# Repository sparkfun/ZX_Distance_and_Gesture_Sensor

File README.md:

**NOTE:** *This product has been retired from our catalog. If you are looking for more up-to-date info, please check out some of these resources to see how other users are still hacking and improving on this product.*
* *[SparkFun Forum](https://forum.sparkfun.com/)*
* *[Comments Here on GitHub](https://github.com/sparkfun/ZX_Distance_and_Gesture_Sensor/issues)*
* *[IRC Channel](https://www.sparkfun.com/news/263)*

There is another version available with the surface mount ICs [ ZX Distance and Gesture Sensor SMD - [SEN-13162](https://www.sparkfun.com/products/13162) ] so the associated Arduino Library will be kept open => [SparkFun_ZX_distance_and_Gesture_Sensor_Arduino_Library](https://github.com/sparkfun/SparkFun_ZX_Distance_and_Gesture_Sensor_Arduino_Library). 

SparkFun ZX Distance and Gesture Sensor
========================================

[*SparkFun ZX Distance and Gesture Sensor (SEN-12780)*](https://www.sparkfun.com/products/12780)

Infrared sensor capable of determining an object's distance from the sensor and its relative position between the IR LEDs. The sensor is capable of determining a 2-dimensional location of an object as well as determining several basic gestures.

Repository Contents
-------------------

* **/Hardware** - Eagle design files (.brd, .sch)
* **/Libraries** - Libraries for use with the ZX Distance and Gesture Sensor
* **/Production** - Production panel files (.brd)

Documentation
--------------

* **[Library](https://github.com/sparkfun/SparkFun_ZX_Distance_and_Gesture_Sensor_Arduino_Library)** - Arduino library for the ZX Distance and Gesture Sensor.
* **[Hookup Guide](https://learn.sparkfun.com/tutorials/zx-distance-and-gesture-sensor-hookup-guide)** - Basic hookup guide for the ZX Distance and Gesture Sensor.
* **[SparkFun Fritzing repo](https://github.com/sparkfun/Fritzing_Parts)** - Fritzing diagrams for SparkFun products.

Product Versions
----------------

* [SEN-12780](https://www.sparkfun.com/products/12780)- ZX Distance and Gesture Sensor

Version History
---------------

* [H_1.0_L_1.0.2](https://github.com/sparkfun/ZX_Distance_and_Gesture_Sensor/tree/H_1.0_L_1.0.2) - Fixed Arduino library name
* [H_1.0_L_1.0.1](https://github.com/sparkfun/ZX_Distance_and_Gesture_Sensor/tree/H_1.0_L_1.0.1) - Fixed typo in Arduino library properties file
* [H_1.0_L_1.0.0](https://github.com/sparkfun/ZX_Distance_and_Gesture_Sensor/tree/H_1.0_L_1.0.0) - Initial release

License Information
-------------------

This product is _**open source**_! 

Please review the LICENSE.md file for license information. 

If you have any questions or concerns on licensing, please contact techsupport@sparkfun.com.

Distributed as-is; no warranty is given.

- Your friends at SparkFun.

_This is a collaboration with [XYZ Interactive](http://www.gesturesense.com/xyz)_

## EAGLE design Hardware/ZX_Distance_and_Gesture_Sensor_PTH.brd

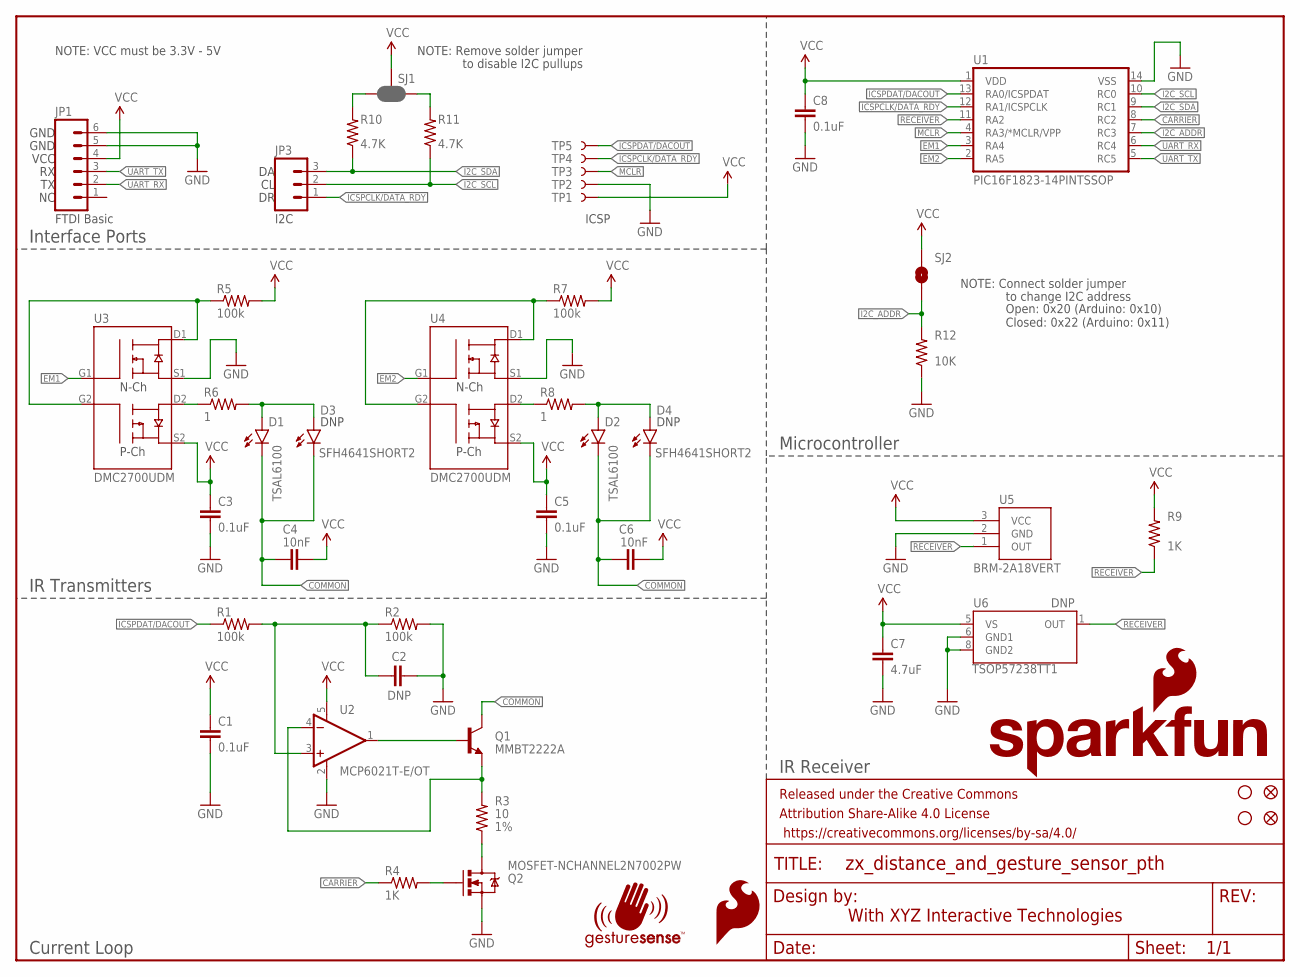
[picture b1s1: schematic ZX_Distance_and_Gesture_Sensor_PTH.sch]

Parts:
C1, C3, C5, C8: 0.1uF; 0603-CAP
C2: DNP; 0603-CAP
C4, C6: 10nF; 0603-CAP
C7: 4.7uF; 0603-CAP
D1, D2: LED-IR-THRUTSAL6100; LED5MM
D3, D4: SFH4641SHORT2; SFH4641-SHORT2
FID1, FID2: FIDUCIAL1X2; FIDUCIAL-1X2
FRAME1: FRAME-LETTER; CREATIVE_COMMONS
JP1: M06NO_SILK_FEMALE_PTH; 1X06_NO_SILK
JP3: M031X03_NO_SILK; 1X03_NO_SILK
LOGO1: SFE_LOGO_FLAME.1_INCH; SFE_LOGO_FLAME_.1
Q1: MMBT2222A; SOT23-3
Q2: MOSFET-NCHANNEL2N7002PW; SOT323
R1, R2, R5, R7: 100k; 0603-RES
R3: 10; 0603-RES
R4, R9: 1K; 0603-RES
R6, R8: 1; 0603-RES
R10, R11: 4.7K; 0603-RES
R12: 10K; 0603-RES
SJ1: JUMPER-PAD-3-NC_BY_PASTE; PAD-JUMPER-3-NC_BY_PASTE_YES_SILK_FULL_BOX
SJ2: JUMPER-PAD-2-NOYES_SILK; PAD-JUMPER-2-NO_YES_SILK
STANDOFF1, STANDOFF2: STAND-OFF
TP1, TP2, TP3, TP4, TP5: TEST-POINT3X4; PAD.03X.04
U1: PIC16F1823-14PINTSSOP; TSSOP14
U2: MCP6021T-E/OT; SOT23-5
U3, U4: DMC2700UDM; SOT26
U5: BRM-2A18VERT; BRM-2508_VERT
U6: TSOP57238TT1; TSOP572
U$5: SFE_LOGO_NAME_FLAME.1_INCH; SFE_LOGO_NAME_FLAME_.1
U$6: GESTURESENSE_LOGOSTEXT; GESTURESENSE_TEXT

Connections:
CARRIER: R4.1, U1.8 (RC2)
COMMON: C4.1, C6.1, D1.K (C), D2.K (C), D3.C, D4.C, Q1.3 (C)
EM1: U1.3 (RA4), U3.G1
EM2: U1.2 (RA5), U4.G1
GND: C1.2, C2.2, C3.2, C5.2, C7.2, C8.2, JP1.5, JP1.6, Q2.2 (S), R2.2, R12.1, TP2.P$1, U1.14 (VSS), U2.2 (V-), U3.S1, U4.S1, U5.2 (GND), U6.6 (GND1), U6.8 (GND2)
I2C_ADDR: R12.2, SJ2.1, U1.7 (RC3)
I2C_SCL: JP3.2, R11.1, U1.10 (RC0)
I2C_SDA: JP3.3, R10.1, U1.9 (RC1)
ICSPCLK/DATA_RDY: JP3.1, TP4.P$1, U1.12 (RA1/ICSPCLK)
ICSPDAT/DACOUT: R1.1, TP5.P$1, U1.13 (RA0/ICSPDAT)
MCLR: TP3.P$1, U1.4 (RA3/*MCLR/VPP)
unnamed: C2.1, R1.2, R2.1, U2.3 (+IN)
unnamed: Q1.2 (E), R3.2, U2.4 (-IN)
unnamed: Q1.1 (B), U2.1 (OUT)
unnamed: Q2.3 (D), R3.1
unnamed: Q2.1 (G), R4.2
unnamed: R6.1, U3.D2
unnamed: D1.A, D3.A, R6.2
unnamed: R5.1, U3.D1, U3.G2
unnamed: R7.1, U4.D1, U4.G2
unnamed: R10.2, SJ1.3
unnamed: R8.1, U4.D2
unnamed: D2.A, D4.A, R8.2
unnamed: R11.2, SJ1.1
RECEIVER: R9.1, U1.11 (RA2), U5.1 (OUT), U6.1 (OUT)
UART_RX: JP1.2, U1.6 (RC4)
UART_TX: JP1.3, U1.5 (RC5)
VCC: C1.1, C3.1, C4.2, C5.1, C6.2, C7.1, C8.1, JP1.4, R5.2, R7.2, R9.2, SJ1.2, SJ2.2, TP1.P$1, U1.1 (VDD), U2.5 (V+), U3.S2, U4.S2, U5.3 (VCC), U6.5 (VS)

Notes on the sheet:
With XYZ Interactive Technologies
FTDI Basic
I2C
ICSP
NOTE: Remove solder jumper
to disable I2C pullups
NOTE: Connect solder jumper
to change I2C address
Open: 0x20 (Arduino: 0x10) Closed: 0x22 (Arduino: 0x11)
Interface Ports
IR Transmitters
Current Loop
Microcontroller
IR Receiver
VCC
GND
DNP
NOTE: VCC must be 3.3V - 5V

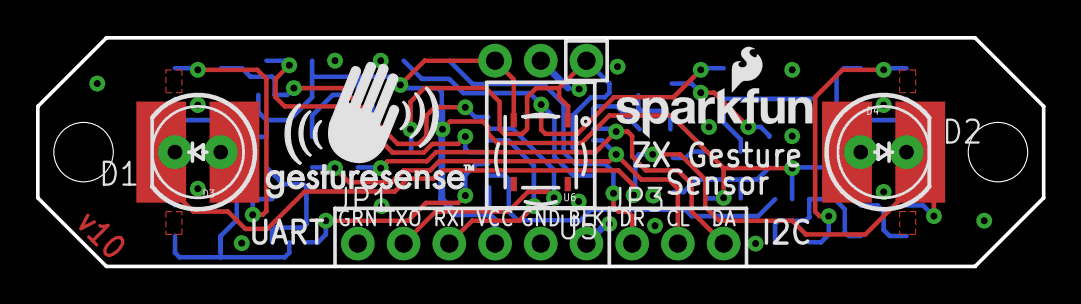
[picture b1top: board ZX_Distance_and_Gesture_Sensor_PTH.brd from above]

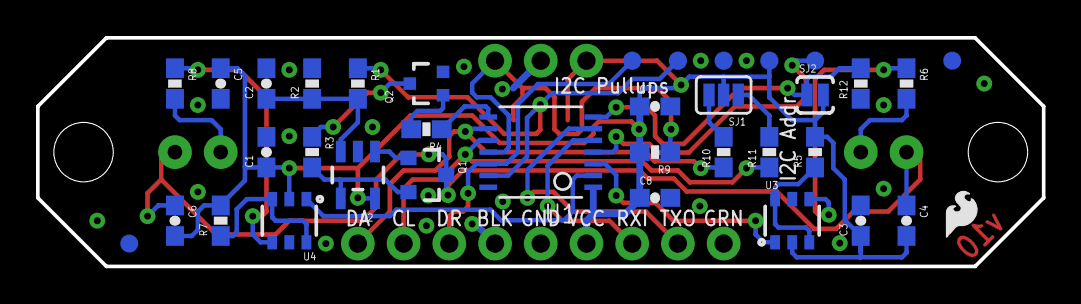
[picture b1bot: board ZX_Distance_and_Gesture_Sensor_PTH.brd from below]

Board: 2 copper layers, 55.9 x 12.7 mm, 49 parts (36 on the bottom side), 28 nets.

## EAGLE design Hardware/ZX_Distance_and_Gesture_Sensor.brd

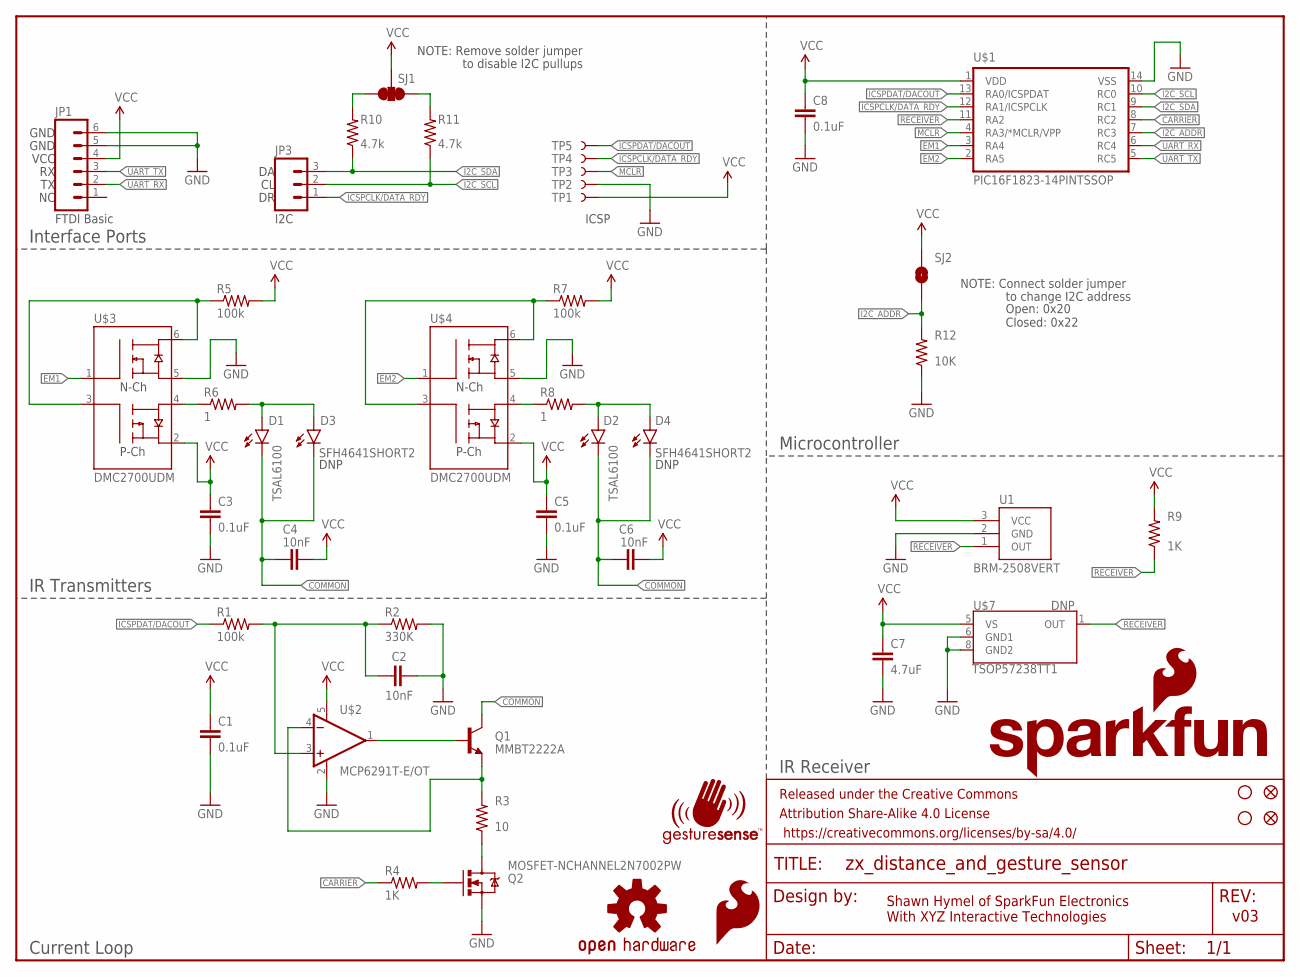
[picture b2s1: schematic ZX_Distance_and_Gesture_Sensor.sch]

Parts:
C1, C3, C5, C8: 0.1uF; 0603-CAP
C2, C4, C6: 10nF; 0603-CAP
C7: 4.7uF; 0603-CAP
D1, D2: LED-IR-THRUTSAL6100; LED5MM
D3, D4: SFH4641SHORT2; SFH4641-SHORT2
FID1, FID2: FIDUCIAL1X2; FIDUCIAL-1X2
FRAME1: FRAME-LETTER; CREATIVE_COMMONS
JP1: M06NO_SILK; 1X06_NO_SILK
JP3: M031X03_NO_SILK; 1X03_NO_SILK
LOGO1: SFE_LOGO_FLAME.1_INCH; SFE_LOGO_FLAME_.1
LOGO2: OSHW-LOGOS; OSHW-LOGO-S
Q1: MMBT2222A; SOT23-3
Q2: MOSFET-NCHANNEL2N7002PW; SOT323
R1, R5, R7: 100k; 0603-RES
R2: 330K; 0603-RES
R3: 10; 0603-RES
R4, R9: 1K; 0603-RES
R6, R8: 1; 0603-RES
R10, R11: 4.7k; 0603
R12: 10K; 0603-RES
SJ1: SOLDERJUMPER_2WAYPASTE1&2&3; SJ_3_PASTE1&2&3
SJ2: SOLDERJUMPERNO; SJ_2S-NO
STANDOFF1, STANDOFF2: STAND-OFF
TP1, TP2, TP3, TP4, TP5: TEST-POINT3X4; PAD.03X.04
U1: BRM-2508VERT; BRM-2508_VERT
U$1: PIC16F1823-14PINTSSOP; TSSOP14
U$2: MCP6291T-E/OT; SOT23-5
U$3, U$4: DMC2700UDM; SOT26
U$5: SFE_LOGO_NAME_FLAME.1_INCH; SFE_LOGO_NAME_FLAME_.1
U$6: GESTURESENSE_LOGOSTEXT; GESTURESENSE_TEXT
U$7: TSOP57238TT1; TSOP572

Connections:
CARRIER: R4.1, U$1.8 (RC2)
COMMON: C4.1, C6.1, D1.K (C), D2.K (C), D3.C, D4.C, Q1.3 (C)
EM1: U$1.3 (RA4), U$3.1 (G1)
EM2: U$1.2 (RA5), U$4.1 (G1)
GND: C1.2, C2.2, C3.2, C5.2, C7.2, C8.2, JP1.5, JP1.6, Q2.2 (S), R2.2, R12.1, TP2.P$1, U1.2 (GND), U$1.14 (VSS), U$2.2 (V-), U$3.5 (S1), U$4.5 (S1), U$7.6 (GND1), U$7.8 (GND2)
I2C_ADDR: R12.2, SJ2.1, U$1.7 (RC3)
I2C_SCL: JP3.2, R11.1, U$1.10 (RC0)
I2C_SDA: JP3.3, R10.1, U$1.9 (RC1)
ICSPCLK/DATA_RDY: JP3.1, TP4.P$1, U$1.12 (RA1/ICSPCLK)
ICSPDAT/DACOUT: R1.1, TP5.P$1, U$1.13 (RA0/ICSPDAT)
MCLR: TP3.P$1, U$1.4 (RA3/*MCLR/VPP)
unnamed: C2.1, R1.2, R2.1, U$2.3 (+IN)
unnamed: Q1.2 (E), R3.2, U$2.4 (-IN)
unnamed: Q1.1 (B), U$2.1 (OUT)
unnamed: Q2.3 (D), R3.1
unnamed: Q2.1 (G), R4.2
unnamed: R6.1, U$3.4 (D2)
unnamed: D1.A, D3.A, R6.2
unnamed: R5.1, U$3.3 (G2), U$3.6 (D1)
unnamed: R7.1, U$4.3 (G2), U$4.6 (D1)
unnamed: R10.2, SJ1.3
unnamed: R8.1, U$4.4 (D2)
unnamed: D2.A, D4.A, R8.2
unnamed: R11.2, SJ1.1
RECEIVER: R9.1, U1.1 (OUT), U$1.11 (RA2), U$7.1 (OUT)
UART_RX: JP1.2, U$1.6 (RC4)
UART_TX: JP1.3, U$1.5 (RC5)
VCC: C1.1, C3.1, C4.2, C5.1, C6.2, C7.1, C8.1, JP1.4, R5.2, R7.2, R9.2, SJ1.2, SJ2.2, TP1.P$1, U1.3 (VCC), U$1.1 (VDD), U$2.5 (V+), U$3.2 (S2), U$4.2 (S2), U$7.5 (VS)

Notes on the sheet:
v03
Shawn Hymel of SparkFun Electronics With XYZ Interactive Technologies
FTDI Basic
I2C
ICSP
NOTE: Remove solder jumper
to disable I2C pullups
NOTE: Connect solder jumper
to change I2C address
Open: 0x20 Closed: 0x22
Interface Ports
IR Transmitters
Current Loop
Microcontroller
IR Receiver
VCC
GND
DNP

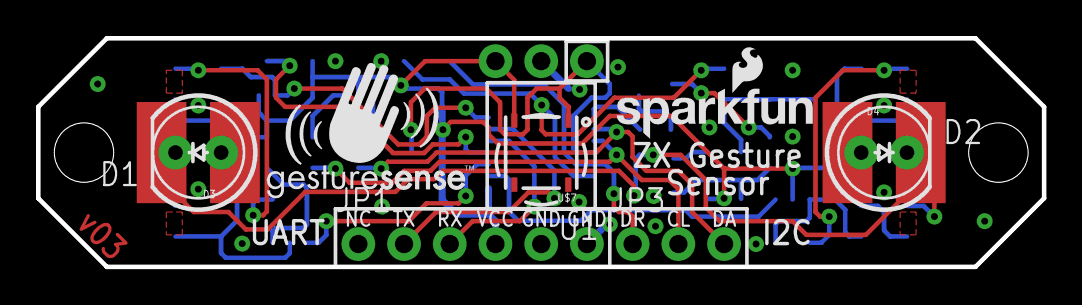
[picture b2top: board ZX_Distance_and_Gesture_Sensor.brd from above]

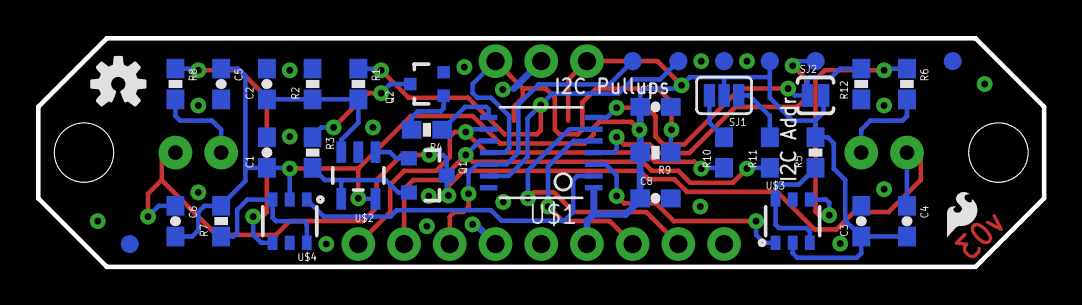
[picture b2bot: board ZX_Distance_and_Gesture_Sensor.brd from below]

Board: 2 copper layers, 55.9 x 12.7 mm, 50 parts (37 on the bottom side), 28 nets.

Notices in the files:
parts and their libraries:
SparkFun-Aesthetics: Licensing: Creative Commons ShareAlike 4.0 International - https://creativecommons.org/licenses/by-sa/4.0
SparkFun-Aesthetics: Released under the Creative Commons Attribution Share-Alike 4.0 License
SparkFun-Aesthetics: https://creativecommons.org/licenses/by-sa/4.0
